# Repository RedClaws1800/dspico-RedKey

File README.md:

## If you've found this then you probably know what the DSpico is

## THIS IS A FORK FROM THE ORIGINAL PROJECT!!!
(https://github.com/LNH-team/dspico-hardware)

## The main purpose of this project:
 Restore the traditional insertion of a game cartridge into the DS console and having the familiar *pop* of the game appearing on the home screen

# THIS PROJECT IS STILL IN DEVELOPMENT 

what follows is the original repo

# DSpico Hardware
## 🗺️ Contents
- [ℹ Introduction](#ℹ-introduction)
- [❔ About this repository](#-about-this-repository).
- [🎮 DSpico PCB](#-dspico-pcb)
- [🧰 DSpico Shell](#-dspico-shell)
- [🎨 Artwork: Stickers and box art](#-artwork-stickers-and-box-art)
- [📦 Instructions](#-instructions)
- [🛠 Development](#-development)
- [👥 Contributions](#-contributions)
- [👾 Discord](#-discord)
- [📋 LNH Team Statement](#-lnh-team-statement)
- [⚖ License](#-license)

## ℹ Introduction
### What is DSpico?
DSpico is the world's first open-source DS(i) flashcart, created by the LNH team. Everything from the PCB, shell, stickers, and box art is open-source. You can either build it yourself as a DIY project or have it made by a manufacturer.

### Features
- RP2040 microcontroller
- 16 Mbit flash memory
- Micro USB port
- Micro SD slot
- Development port
- Two LEDs (red and blue)
- Dual power support: can be powered by USB and DS simultaneously (by ORing circuit)

With the [DSpico Firmware](https://github.com/LNH-team/dspico-firmware):
- Sequential SD read speed: up to 6MB/s
- Power consuption: ~57 mW
- Compatible with DSi mode
- Compatible with [Pico Loader](https://github.com/LNH-team/pico-loader) and [Pico Launcher](https://github.com/LNH-team/pico-launcher)

## ❔ About this repository
This repository contains the necessary files for the hardware of the DSpico, including a PCB, CAD design of the shell, stickers for cartridge and box art.

## 🎮 DSpico PCB
The PCB design is located in the [`dspico-pcb`](dspico-pcb) folder. This folder contains all the necessary files for PCB fabrication, as well as the design files created using the electronic design software.

### 📂 Included Subfolders:
- [`design-files`](dspico-pcb/design-files): PCB schematic and layout of DSpico. (KiCad format)
- [`fabrication-files`](dspico-pcb/fabrication-files): Gerber files, Pick&Place files and BOM for PCB fabrication of DSpico.
- [`docs`](dspico-pcb/docs): Documentation for manufacturing and assembling DSpico.

### 🔌 Pinout

| **Peripheral**  | **Pin name - Peripheral** | **Pin name - RP2040** | **Pin number - RP2040** |
|-------------|-----------------------|-------------------|-------------|
| **DS Slot** | D0                    | GPIO12            | 15          |
|             | D1                    | GPIO13            | 16          |
|             | D2                    | GPIO14            | 17          |
|             | D3                    | GPIO15            | 18          |
|             | D4                    | GPIO16            | 27          |
|             | D5                    | GPIO17            | 28          |
|             | D6                    | GPIO18            | 29          |
|             | D7                    | GPIO19            | 30          |
|             | CLK_DS                | GPIO11            | 14          |
|             | ROM_CS                | GPIO10            | 13          |
|             | SPI_CS                | GPIO21            | 32          |
|             | IRQ                   | GPIO20            | 31          |
|             | RST_DS                | GPIO09            | 12          |
| **SD slot**| CLK_SD                | GPIO03            | 5           |
|             | DAT0                  | GPIO05            | 7           |
|             | DAT1                  | GPIO06            | 8           |
|             | DAT2                  | GPIO07            | 9           |
|             | DAT3                  | GPIO08            | 11          |
|             | CMD                   | GPIO04            | 6           |
| **DEV port**| SWD                   | SWD               | 25          |
|             | SWCLK                 | SWCLK             | 24          |
|             | TX                    | GPIO0            | 2           |
|             | RX                    | GPIO1            | 3           |
| **Blue LED**   | LED_B                 | GPIO28            | 40          |
| **Red LED**   | LED_R                 | GPIO27            | 39          |

## 🧰 DSpico Shell

The CAD design of the shell is located in the [`dspico-shell`](dspico-shell) folder. This folder contains 3D models of the shell (output 3d models and design files), which can be viewed and modified using CAD design software Autodesk Inventor

### 📂 Included Subfolders:
- [`design-files`](dspico-shell/design-files): Contains source design files for the shell
- [`3d-models`](dspico-shell/3d-models): Contains 3D models of the shell in STL and STEP format for fabrication.

## 🎨 Artwork: Stickers and box art
The stickers and box art design are located in the [`dspico-artwork-design`](dspico-artwork-design).  This folder contains stickers for cartridge and box art in SVG, PSD and PNG formats.

### 📂 Included Subfolders:
- [`stickers`](dspico-artwork-design/stickers): Stickers to print and put on your DSpico cartridge.
- [`box-art`](dspico-artwork-design/box-art): Box art design to print and put on your DS box.
- [`logo`](dspico-artwork-design/logo): DSpico logo in different formats.
- [`others`](dspico-artwork-design/others): Other graphics related to DSpico

## 📦 Instructions
### 1️⃣ Build
1. **Manufacture the PCB and Shell**<br>
    Start by producing both the PCB and the shell. Go to the respective sections, [`dspico-pcb`](dspico-pcb) and [`dspico-shell`](dspico-shell), and read the README file in each to understand how to create these parts.

2. **Optional: Customize with a Sticker and Box Art**<br>
    If desired, you can print a sticker from the stickers section and add box art [`dspico-artwork-design`](dspico-artwork-design) for storing your DSpico (for example, by reusing an existing box).

### 2️⃣ Assembly
Once you have both the PCB and the shell manufactured, the next step is to assemble them. Follow these steps:
1. First, insert the PCB into the bottom part of the shell.
2. Next, attach the top part of the shell by aligning the pegs with the holes in the bottom part.
3. Stick your favorite DSpico sticker on top part.
Make sure everything fits, and your DSpico will be ready for the next steps!

### 3️⃣ Setup the software
Follow the [guide](https://github.com/LNH-team/dspico/blob/develop/GUIDE.md) for instructions on how to compile and setup the firmware and the contents of the micro SD card.

## 🛠 Development
The DSpico features a development port for creating new applications and developing new peripherals. The available communication ports are as follows:
- UART
- I2C
- x2 GPIO
- SWD (debug)

As for the power it can provide to peripherals, it is:
- 3.3 V (up to 50 mA)

The pitch between pins of this port is 2.54 mm such that some connectors can be soldered (as long as it does not interfere with the rest of the DSpico mechanics). For example a male or female header.

## 👥 Contributions

Contributions are welcome. If you wish to improve the PCB or shell designs, feel free to submit a pull request!

### Contributors:

#### PCB:
 - [nitehack](https://www.github.com/nitehack)
 - [Gericom](https://github.com/Gericom) (first DSpico prototype)

#### Shell:
 - rcuevas
 - [nitehack](https://www.github.com/nitehack)

#### Artworks:
 - [nitehack](https://www.github.com/nitehack)

## 👾 Discord
- [DS⁽ⁱ⁾ Mode Hacking!](https://discord.gg/fCzqcWteC4)

## 📋 LNH Team Statement
We wish to make it clear that the LNH team has no affiliation with any commercial projects, and we do not endorse or engage in any for-profit endeavors concerning DSpico or related materials. This statement serves as a formal disavowal of any financial or business dealings that may arise in relation to DSpico, and we take no responsibility for any actions or transactions carried out by third parties in this regard.

## ⚖ License

This project is licensed under the CC BY-SA 4.0 License. See the [`LICENSE`](LICENSE) file for more details.

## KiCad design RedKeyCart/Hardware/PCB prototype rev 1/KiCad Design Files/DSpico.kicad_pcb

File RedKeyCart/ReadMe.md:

### Hoi, Im Red.

and this is a fork

what follows is a readme about the actual end goal

there is another file called "DevLog" that contains detailed info on the whole creation process

this read me is gunna look like shit and im sorry

the whole point of this project is to restore the fun inserting of carts into the DS on a fully modded console.

THIS IS   **N O T**   A WAY TO PIRATE GAMES

the way this system will work is by using the RP2040 and its memory to store a code of which i haven't decided. and this code will be read by custom software loaded onto the DS and will reference a table stored on the SD card and find the corresponding game associated with the ID stored within the cartrage.
That game gets piped into the cartrage slot on the home screen of the DS making the game and its associated cartrage behave like an original unmodded setup.

if you think that is cool and something you'd be interested in then stick around

Please note: This project is in a extremely early state with virtually nothing to show for it

Looking for C/C++ programmers, will pay

Looking for ARM assembly programmers to hug and pay

if you like my dumb writing style please feel free to read the Dev Log

<3

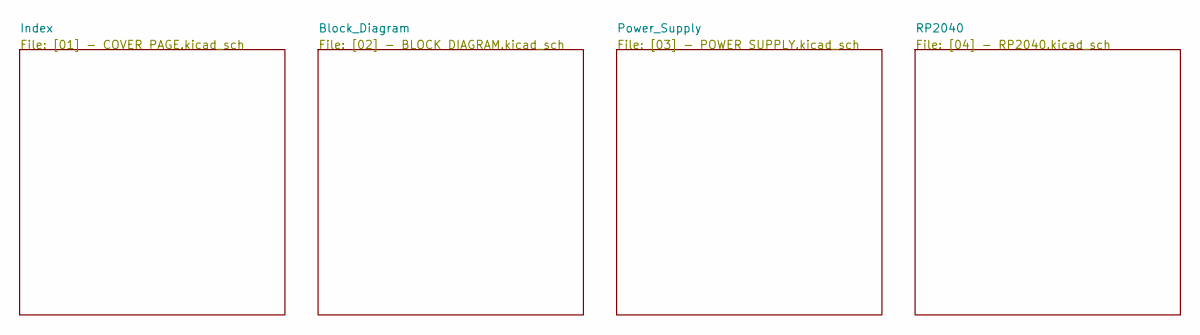
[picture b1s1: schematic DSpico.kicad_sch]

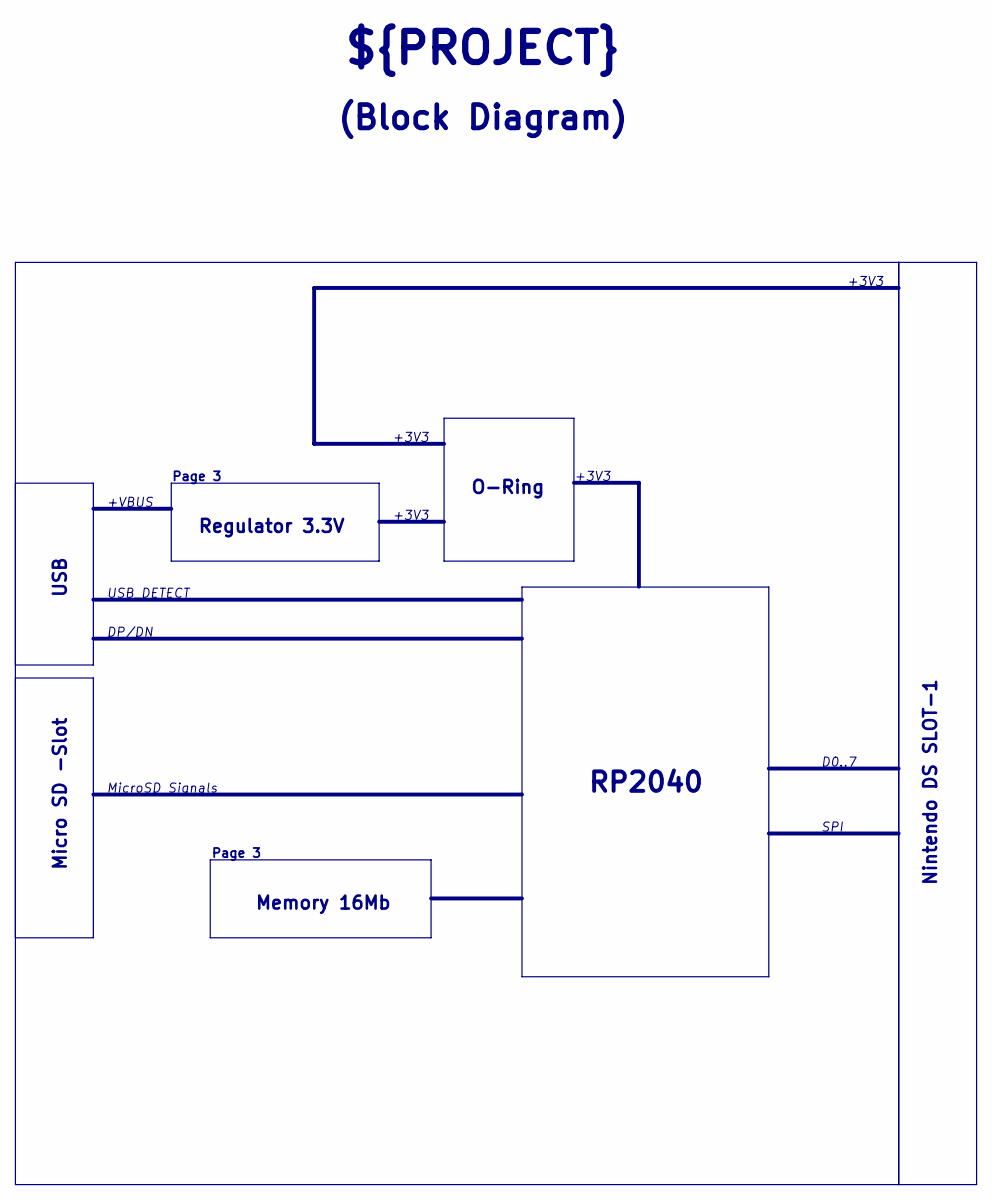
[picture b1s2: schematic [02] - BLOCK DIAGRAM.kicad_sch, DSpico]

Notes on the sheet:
+VBUS
+3V3
RP2040
Page 3
(Block Diagram)
USB_DETECT
D0..7
SPI
O-Ring
USB
MicroSD Signals
Regulator 3.3V
Nintendo DS SLOT-1
DP/DN
${PROJECT}
Micro SD -Slot
Memory 16Mb

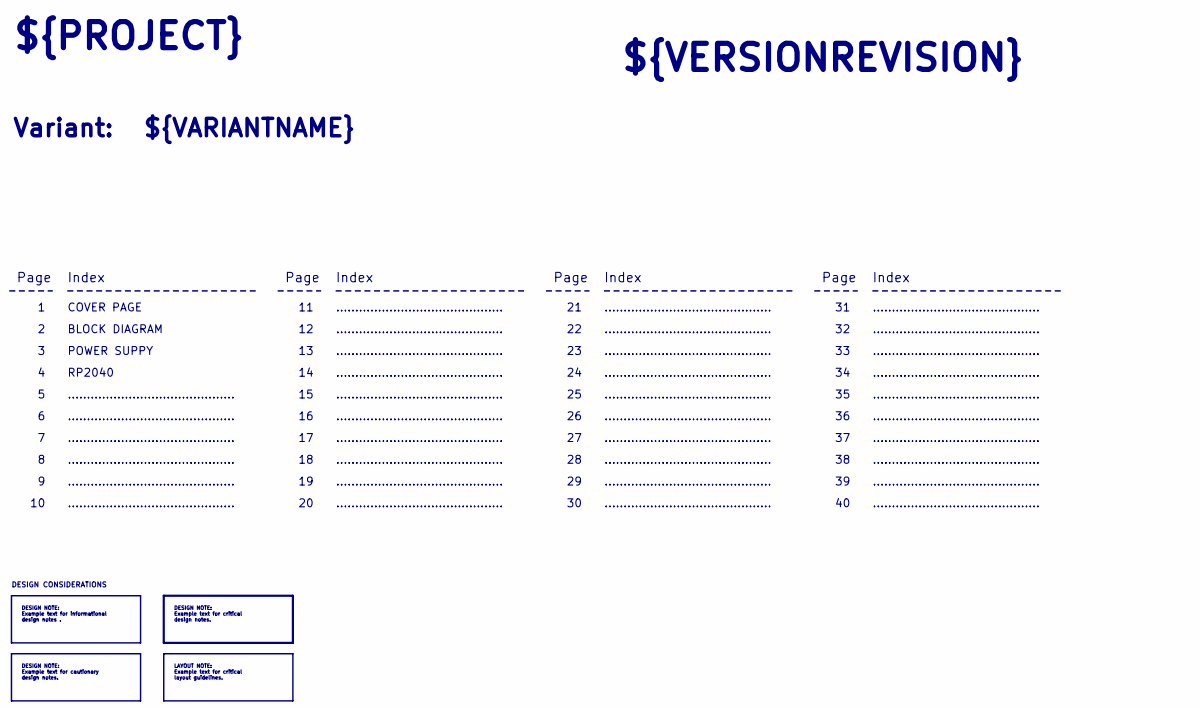
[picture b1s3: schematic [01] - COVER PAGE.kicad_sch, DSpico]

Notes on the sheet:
Page
............................................
POWER SUPPY
COVER PAGE
${VARIANTNAME}
Index
BLOCK DIAGRAM
${PROJECT}
DESIGN CONSIDERATIONS
RP2040
${VERSIONREVISION}
Variant:
DESIGN NOTE: Example text for cautionary design notes.
DESIGN NOTE: Example text for informational design notes .
DESIGN NOTE: Example text for critical design notes.
LAYOUT NOTE: Example text for critical layout guidelines.

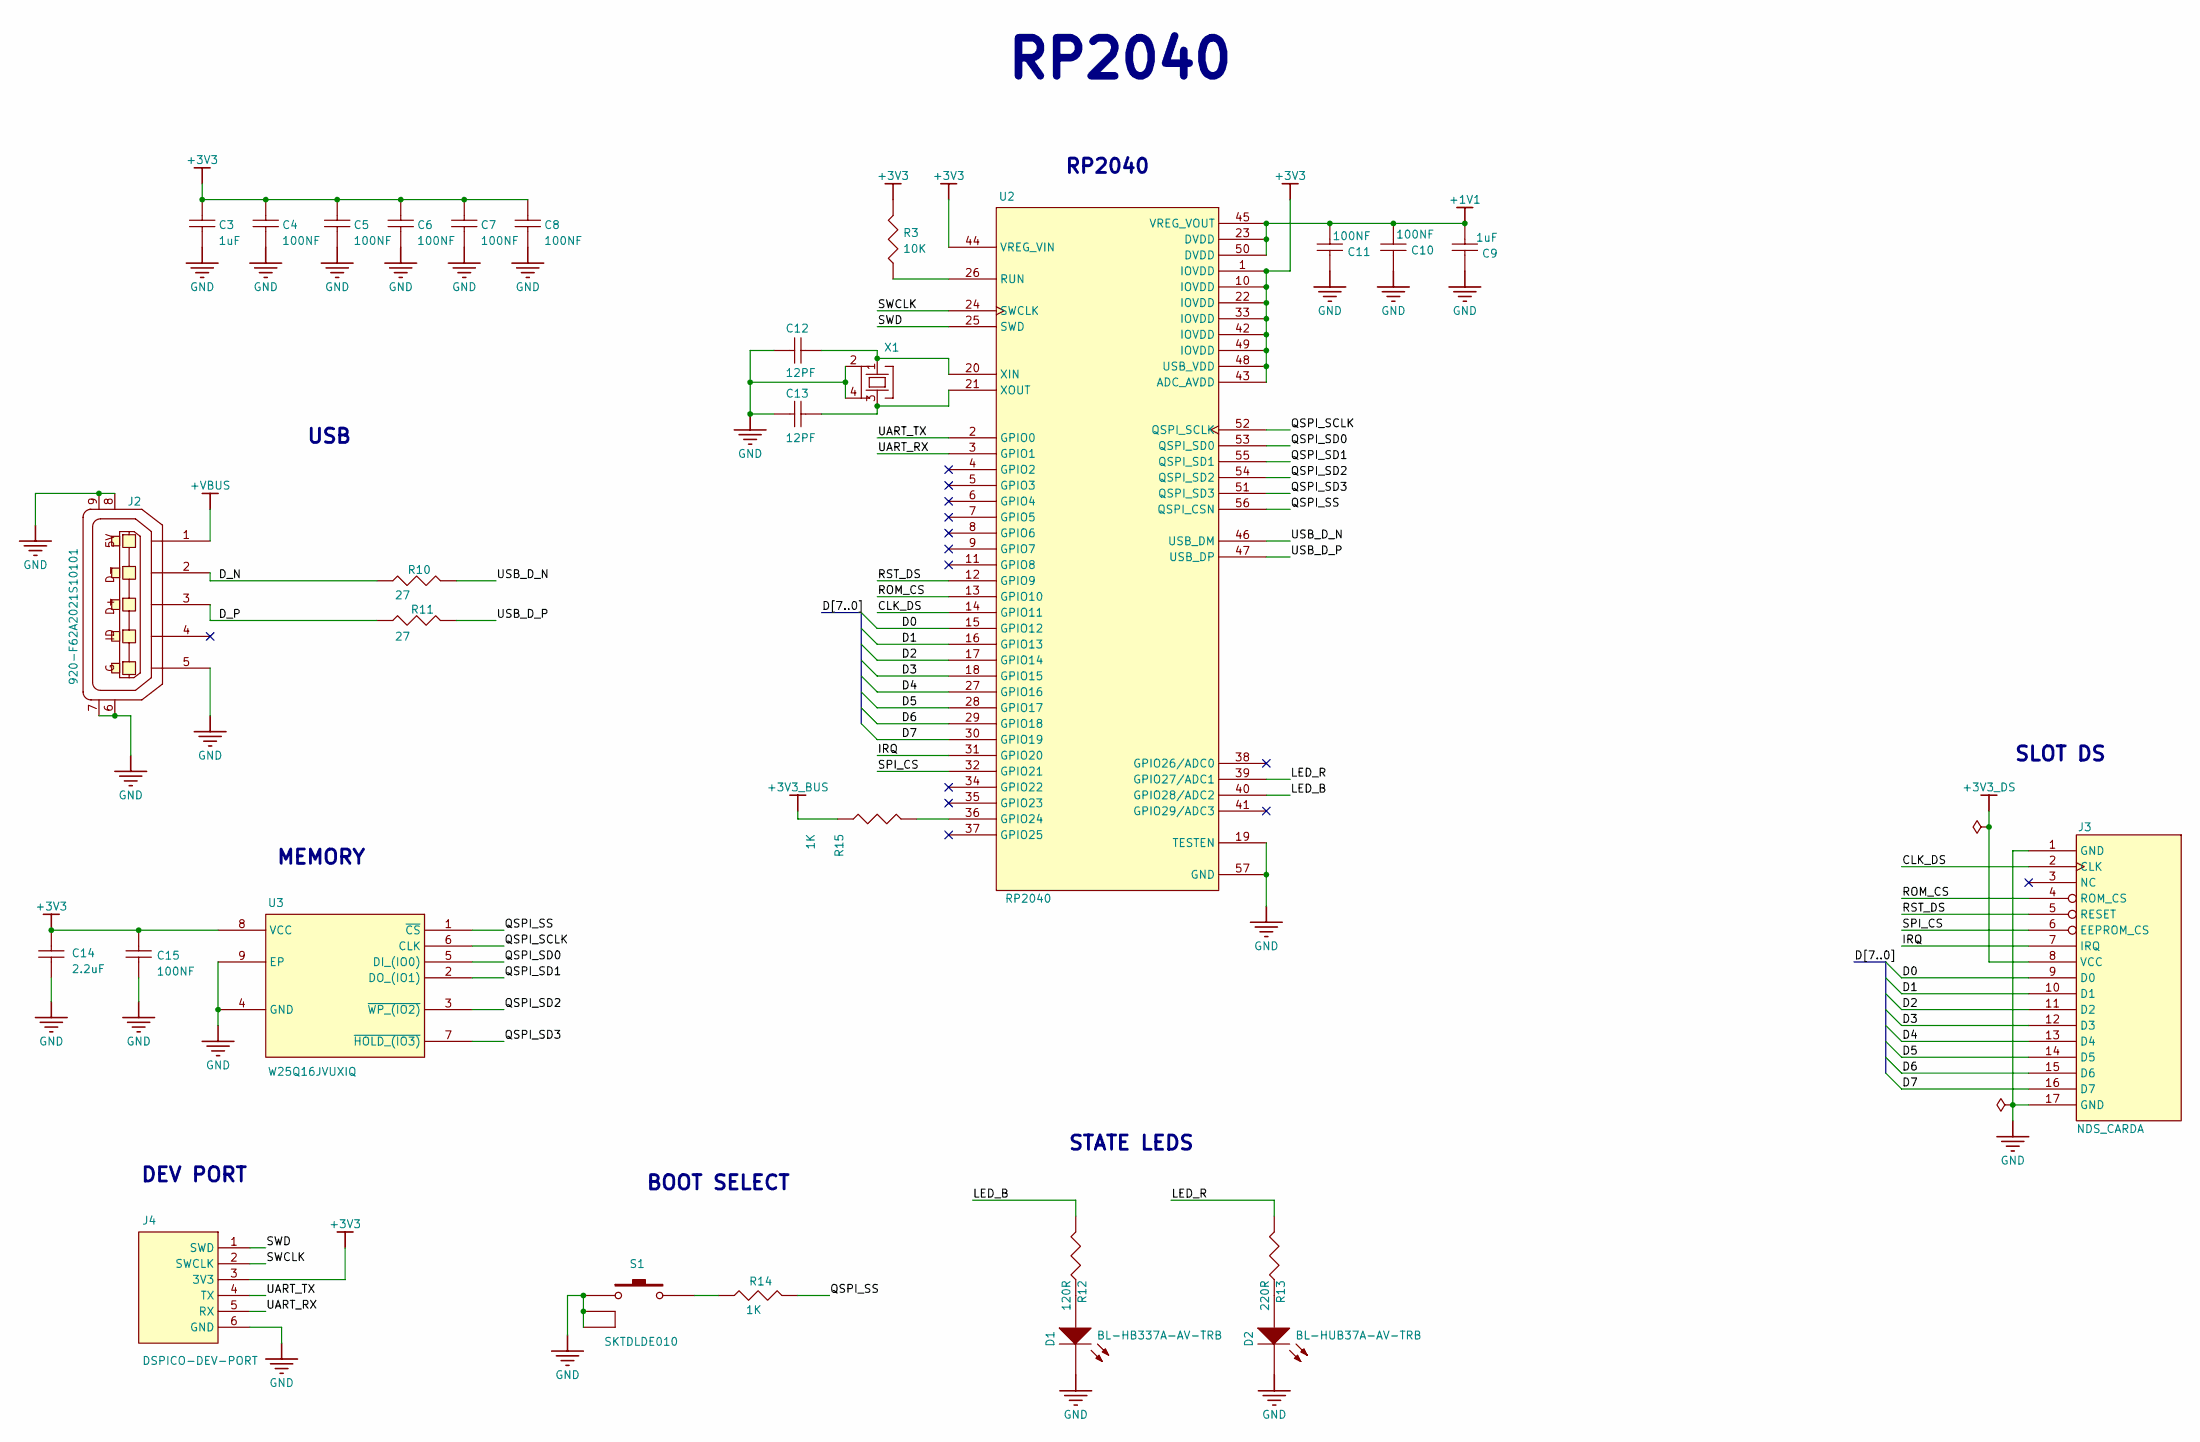
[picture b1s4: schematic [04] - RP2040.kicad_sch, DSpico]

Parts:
C3, C9: 1uF; C0402; TOLERANCE 10%; VOLTAGE RATING 25V; MANUFACTURER PART NUMBER C1005X5R1E105K050BC
C4, C5, C6, C7, C8, C10, C11, C15: 100NF; C0402; TOLERANCE 10%; VOLTAGE RATING 16V; MANUFACTURER PART NUMBER GRM155R71C104KA88D
C12, C13: 12PF; C0402; TOLERANCE 5%; VOLTAGE RATING 50V; MANUFACTURER PART NUMBER 04025A120JAT2A
C14: 2.2uF; C0402; MANUFACTURER PART NUMBER C1005X5R1A225K050BC
D1: BL-HB337A-AV-TRB; LED0402-RD; FORWARD VOLTAGE 2.8V; MANUFACTURER PART NUMBER BL-HB337A-AV-TRB
D2: BL-HUB37A-AV-TRB; LED0402-RD; FORWARD VOLTAGE 2V; MANUFACTURER PART NUMBER BL-HUB37A-AV-TRB
J2: 920-F62A2021S10101; MICRO-USB_MICRO-USB-31
J3: NDS_CARDA; NDS_CARD
J4: DSPICO-DEV-PORT; EP_DEV_PORT; CURRENT RATING ?; VOLTAGE RATING 3.3V; MANUFACTURER PART NUMBER PICO-DEVELOP-PORT
R3: 10K; R0402; TOLERANCE 1%; POWER RATING 63mW; MANUFACTURER PART NUMBER CRCW040210K0FKED
R10, R11: RC0402FR-0727RL; R0402; WORKING VOLTAGE 50V; TOLERANCE 1%
R12: 120R; R0402; VOLTAGE RATING 50V; POWER RATING 62.5mW; MANUFACTURER PART NUMBER RC0402FR-07120RL
R13: 220R; R0402; VOLTAGE RATING 50V; POWER RATING 62.5mW; MANUFACTURER PART NUMBER RC0402FR-07220RL
R14, R15: 1K; R0402; TOLERANCIA DE RESISTENC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 ± 1%; MANUFACTURER PART NUMBER CRCW04021K00FKED
S1: SKTDLDE010; KEY-SMD_SKTDLDE010; MANUFACTURER PART NUMBER SKTDLDE010
U2: RP2040; QFN40P700X700X90-57N
U3: W25Q16JVUXIQ; SON50P300X200X60-9N
X1: XYDBPCNANF-12MHZ; OSC-SMD_4P-L2.5-W2.0-BL

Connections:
+1V1: C9.2, C10.2, C11.2, U2.23 (DVDD), U2.45 (VREG_VOUT), U2.50 (DVDD)
+3V3: C3.2, C4.2, C5.2, C6.2, C7.2, C8.2, C14.2, C15.2, J4.3 (3V3), R3.2, U2.1 (IOVDD), U2.10 (IOVDD), U2.22 (IOVDD), U2.33 (IOVDD), U2.42 (IOVDD), U2.43 (ADC_AVDD), U2.44 (VREG_VIN), U2.48 (USB_VDD), U2.49 (IOVDD), U3.8 (VCC); also elsewhere on the board
+3V3_BUS: R15.1; also elsewhere on the board
+3V3_DS: J3.8 (VCC); also elsewhere on the board
+VBUS: J2.1; also elsewhere on the board
/RP2040/CLK_DS: J3.2 (CLK), U2.14 (GPIO11)
/RP2040/D0: J3.9 (D0), U2.15 (GPIO12)
/RP2040/D1: J3.10 (D1), U2.16 (GPIO13)
/RP2040/D2: J3.11 (D2), U2.17 (GPIO14)
/RP2040/D3: J3.12 (D3), U2.18 (GPIO15)
/RP2040/D4: J3.13 (D4), U2.27 (GPIO16)
/RP2040/D5: J3.14 (D5), U2.28 (GPIO17)
/RP2040/D6: J3.15 (D6), U2.29 (GPIO18)
/RP2040/D7: J3.16 (D7), U2.30 (GPIO19)
/RP2040/D_N: J2.2, R10.1
/RP2040/D_P: J2.3, R11.1
/RP2040/IRQ: J3.7 (IRQ), U2.31 (GPIO20)
/RP2040/LED_B: R12.2, U2.40 (GPIO28/ADC2)
/RP2040/LED_R: R13.2, U2.39 (GPIO27/ADC1)
/RP2040/QSPI_SCLK: U2.52 (QSPI_SCLK), U3.6 (CLK)
/RP2040/QSPI_SD0: U2.53 (QSPI_SD0), U3.5 (DI_(IO0))
/RP2040/QSPI_SD1: U2.55 (QSPI_SD1), U3.2 (DO_(IO1))
/RP2040/QSPI_SD2: U2.54 (QSPI_SD2), U3.3 (~WP_(IO2))
/RP2040/QSPI_SD3: U2.51 (QSPI_SD3), U3.7 (~HOLD_(IO3))
/RP2040/QSPI_SS: R14.2, U2.56 (QSPI_CSN), U3.1 (~CS)
/RP2040/ROM_CS: J3.4 (ROM_CS), U2.13 (GPIO10)
/RP2040/RST_DS: J3.5 (RESET), U2.12 (GPIO9)
/RP2040/SPI_CS: J3.6 (EEPROM_CS), U2.32 (GPIO21)
/RP2040/SWCLK: J4.2 (SWCLK), U2.24 (SWCLK)
/RP2040/SWD: J4.1 (SWD), U2.25 (SWD)
/RP2040/UART_RX: J4.5 (RX), U2.3 (GPIO1)
/RP2040/UART_TX: J4.4 (TX), U2.2 (GPIO0)
/RP2040/USB_D_N: R10.2, U2.46 (USB_DM)
/RP2040/USB_D_P: R11.2, U2.47 (USB_DP)
GND: C3.1, C4.1, C5.1, C6.1, C7.1, C8.1, C9.1, C10.1, C11.1, C12.1, C13.1, C14.1, C15.1, D1.1, D2.1, J2.5, J2.6, J2.7, J2.8, J2.9, J3.1 (GND), J3.17 (GND), J4.6 (GND), S1.1, S1.3, S1.4, U2.19 (TESTEN), U2.57 (GND), U3.4 (GND), U3.9 (EP), X1.2, X1.4; also elsewhere on the board
unnamed: D1.2, R12.1
unnamed: D2.2, R13.1
unnamed: R14.1, S1.2
unnamed: R15.2, U2.36 (GPIO24)
unnamed: R3.1, U2.26 (RUN)
unnamed: C12.2, U2.20 (XIN), X1.1
unnamed: C13.2, U2.21 (XOUT), X1.3

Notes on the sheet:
MEMORY
BOOT SELECT
RP2040
SLOT DS
STATE LEDS
DEV PORT
USB

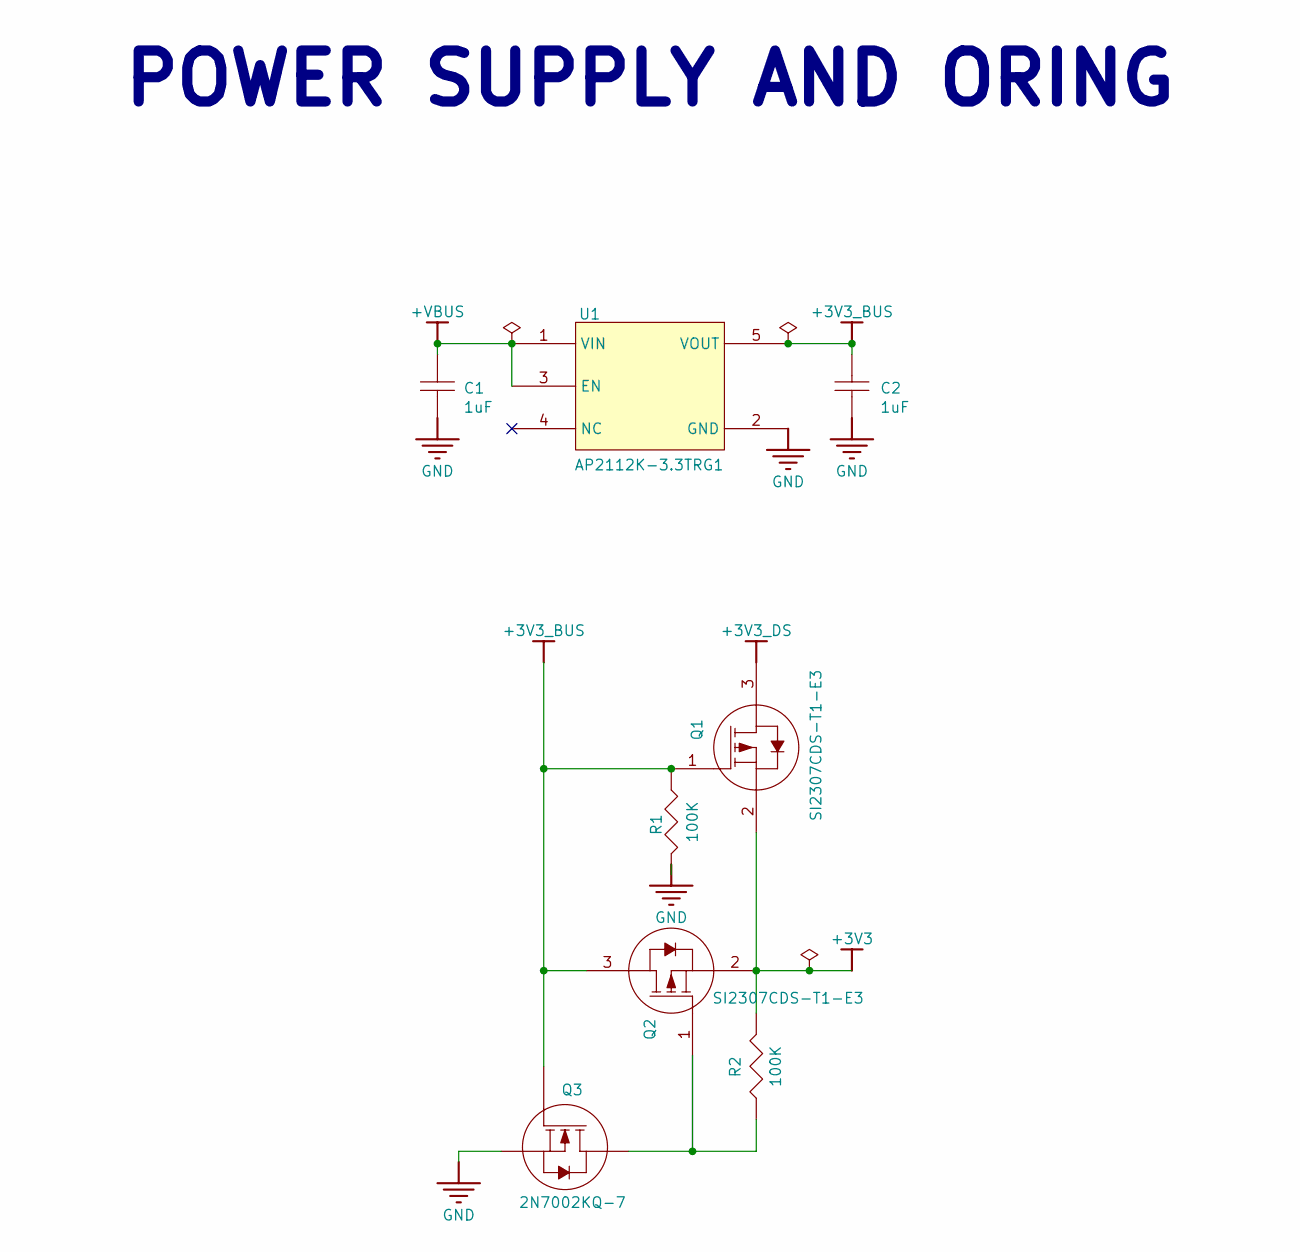
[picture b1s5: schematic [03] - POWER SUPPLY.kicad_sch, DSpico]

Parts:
C1, C2: 1uF; C0402; TOLERANCE 10%; VOLTAGE RATING 25V; MANUFACTURER PART NUMBER C1005X5R1E105K050BC
Q1, Q2: SI2307CDS-T1-E3; SOT-23_L2.9-W1.3-P1.90-LS2.4-BR
Q3: 2N7002KQ-7; SOT-23_L2.9-W1.3-P1.90-LS2.4-BR; MANUFACTURER PART NUMBER 2N7002KQ-7
R1, R2: 100K; R0402; TOLERANCE 1%; POWER RATING 63mW; MANUFACTURER PART NUMBER CRCW0402100KFKED
U1: AP2112K-3.3TRG1; SOT95P285X140-5N; DROPOUT VOLTAGE 250mV; OUTPUT VOLTAGE 3.3V; MANUFACTURER PART NUMBER AP2112K-3.3TRG1

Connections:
+3V3: Q1.2 (S), Q2.2 (S), R2.2; also elsewhere on the board
+3V3_BUS: C2.2, Q1.1 (G), Q2.3 (D), Q3.1 (G), R1.1, U1.5 (VOUT); also elsewhere on the board
+3V3_DS: Q1.3 (D); also elsewhere on the board
+VBUS: C1.2, U1.1 (VIN), U1.3 (EN); also elsewhere on the board
GND: C1.1, C2.1, Q3.2 (S), R1.2, U1.2 (GND); also elsewhere on the board
unnamed: Q2.1 (G), Q3.3 (D), R2.1

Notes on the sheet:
POWER SUPPLY AND ORING

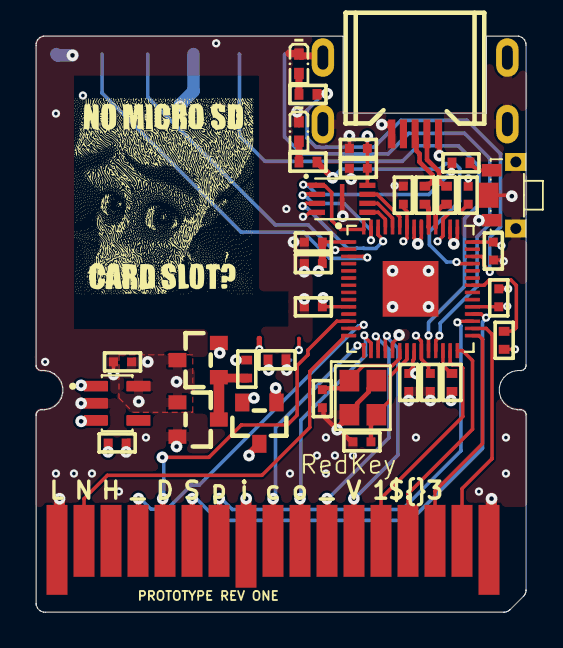
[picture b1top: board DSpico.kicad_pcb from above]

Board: 4 copper layers, 27.2 x 32.0 mm, 37 parts (1 on the bottom side), 43 nets.
